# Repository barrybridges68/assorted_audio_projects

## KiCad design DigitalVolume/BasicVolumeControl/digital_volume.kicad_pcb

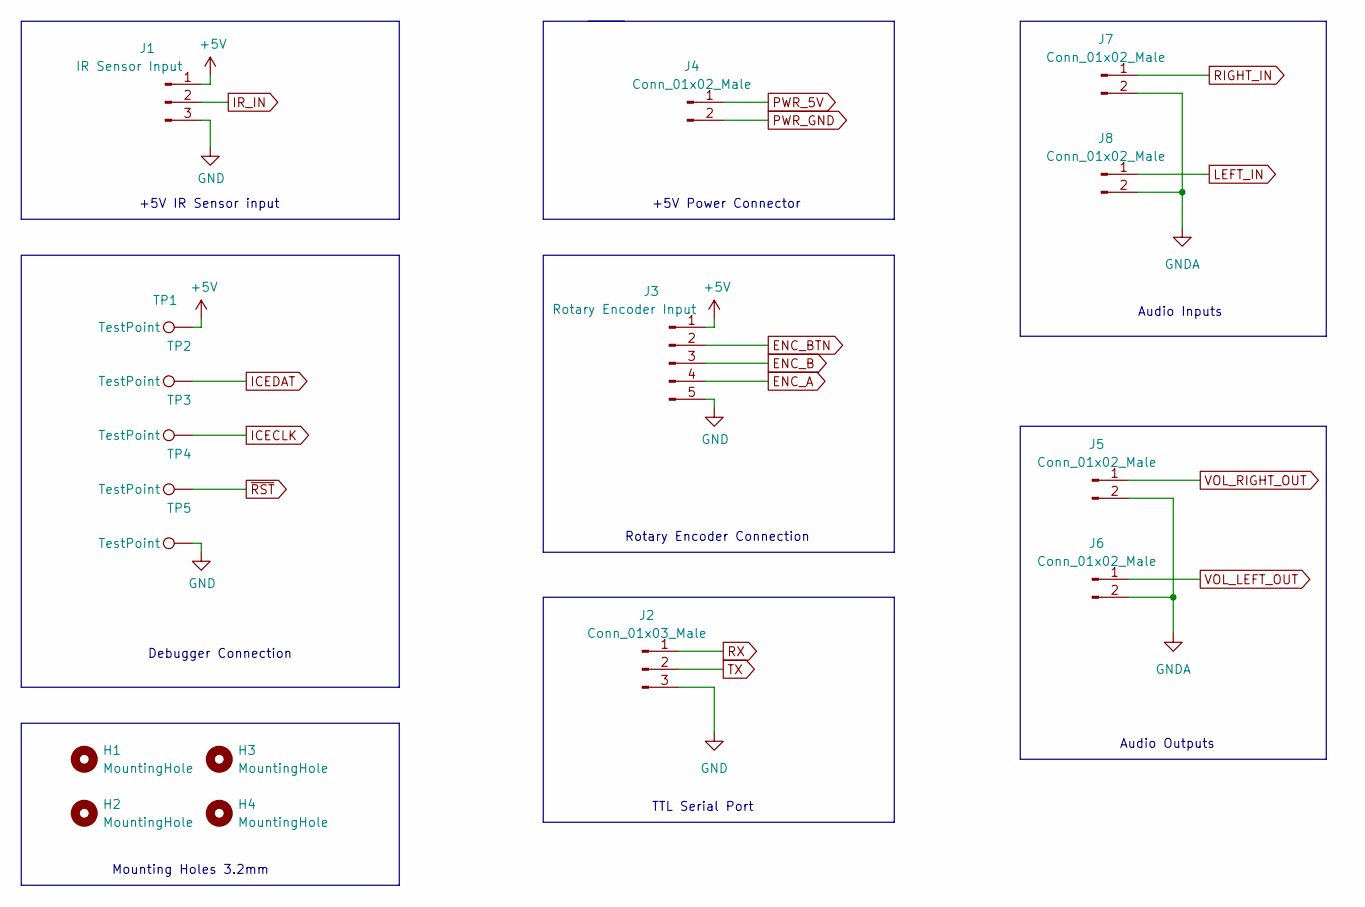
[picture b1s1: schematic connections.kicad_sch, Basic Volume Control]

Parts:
H1, H2, H3, H4: MountingHole; MountingHole_3.2mm_M3
J1: IR Sensor Input; JST_EH_B3B-EH-A_1x03_P2.50mm_Vertical
J2: Conn_01x03_Male; JST_EH_B3B-EH-A_1x03_P2.50mm_Vertical
J3: Rotary Encoder Input; JST_EH_B5B-EH-A_1x05_P2.50mm_Vertical
J4, J5, J6, J7, J8: Conn_01x02_Male; JST_EH_B2B-EH-A_1x02_P2.50mm_Vertical
TP1, TP2, TP3, TP4, TP5: TestPoint; TestPoint_Pad_1.0x1.0mm

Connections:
+5V: J1.1, J3.1, TP1.1; also elsewhere on the board
ENC_A: J3.4; also elsewhere on the board
ENC_B: J3.3; also elsewhere on the board
ENC_BTN: J3.2; also elsewhere on the board
ICECLK: TP3.1; also elsewhere on the board
ICEDAT: TP2.1; also elsewhere on the board
IR_IN: J1.2; also elsewhere on the board
LEFT_IN: J8.1; also elsewhere on the board
PWR_5V: J4.1; also elsewhere on the board
PWR_GND: J1.3, J2.3, J3.5, J4.2, J5.2, J6.2, J7.2, J8.2, TP5.1; also elsewhere on the board
RIGHT_IN: J7.1; also elsewhere on the board
RX: J2.1; also elsewhere on the board
TX: J2.2; also elsewhere on the board
VOL_LEFT_OUT: J6.1; also elsewhere on the board
VOL_RIGHT_OUT: J5.1; also elsewhere on the board
~RST: TP4.1; also elsewhere on the board

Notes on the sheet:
+5V IR Sensor input
Audio Outputs
Mounting Holes 3.2mm
Audio Inputs
Debugger Connection
+5V Power Connector
TTL Serial Port
Rotary Encoder Connection

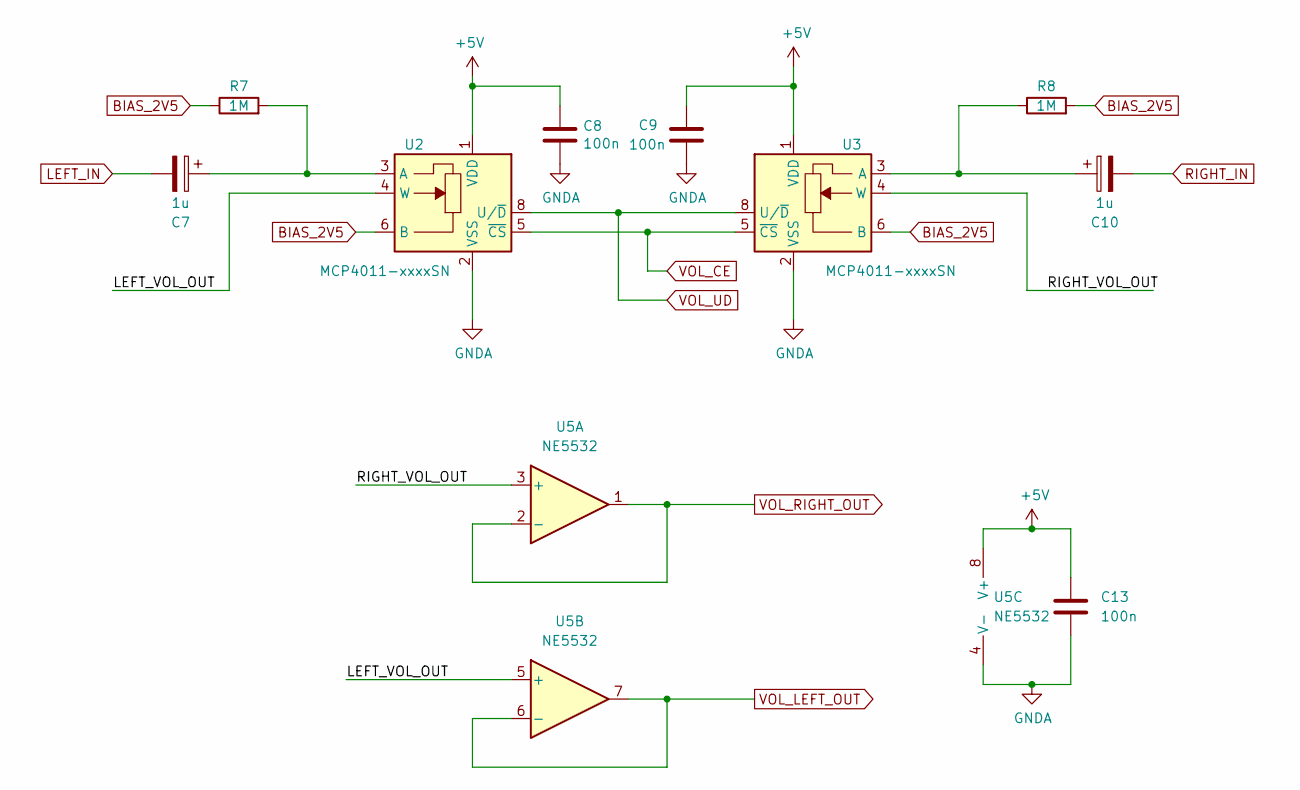
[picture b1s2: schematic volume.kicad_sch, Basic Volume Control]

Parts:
C7, C10: 1u; CP_Elec_4x5.4
C8, C9, C13: 100n; C_0603_1608Metric
R7, R8: 1M; R_0603_1608Metric
U2, U3: MCP4011-xxxxSN; SOIC-8_3.9x4.9mm_P1.27mm
U5: NE5532; SOIC-8_3.9x4.9mm_P1.27mm

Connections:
+5V: C8.1, C9.1, C13.1, U2.1 (VDD), U3.1 (VDD), U5.8 (V+); also elsewhere on the board
/volume/LEFT_VOL_OUT: U2.4 (W), U5.5 (+)
/volume/RIGHT_VOL_OUT: U3.4 (W), U5.3 (+)
BIAS_2V5: R7.1, R8.2, U2.6 (B), U3.6 (B); also elsewhere on the board
LEFT_IN: C7.2; also elsewhere on the board
unnamed: C7.1, R7.2, U2.3 (A)
unnamed: C10.1, R8.1, U3.3 (A)
PWR_GND: C8.2, C9.2, C13.2, U2.2 (VSS), U3.2 (VSS), U5.4 (V-); also elsewhere on the board
RIGHT_IN: C10.2; also elsewhere on the board
VOL_CE: U2.5 (~CS), U3.5 (~CS); also elsewhere on the board
VOL_LEFT_OUT: U5.6 (-), U5.7; also elsewhere on the board
VOL_RIGHT_OUT: U5.1, U5.2 (-); also elsewhere on the board
VOL_UD: U2.8 (U/~D), U3.8 (U/~D); also elsewhere on the board

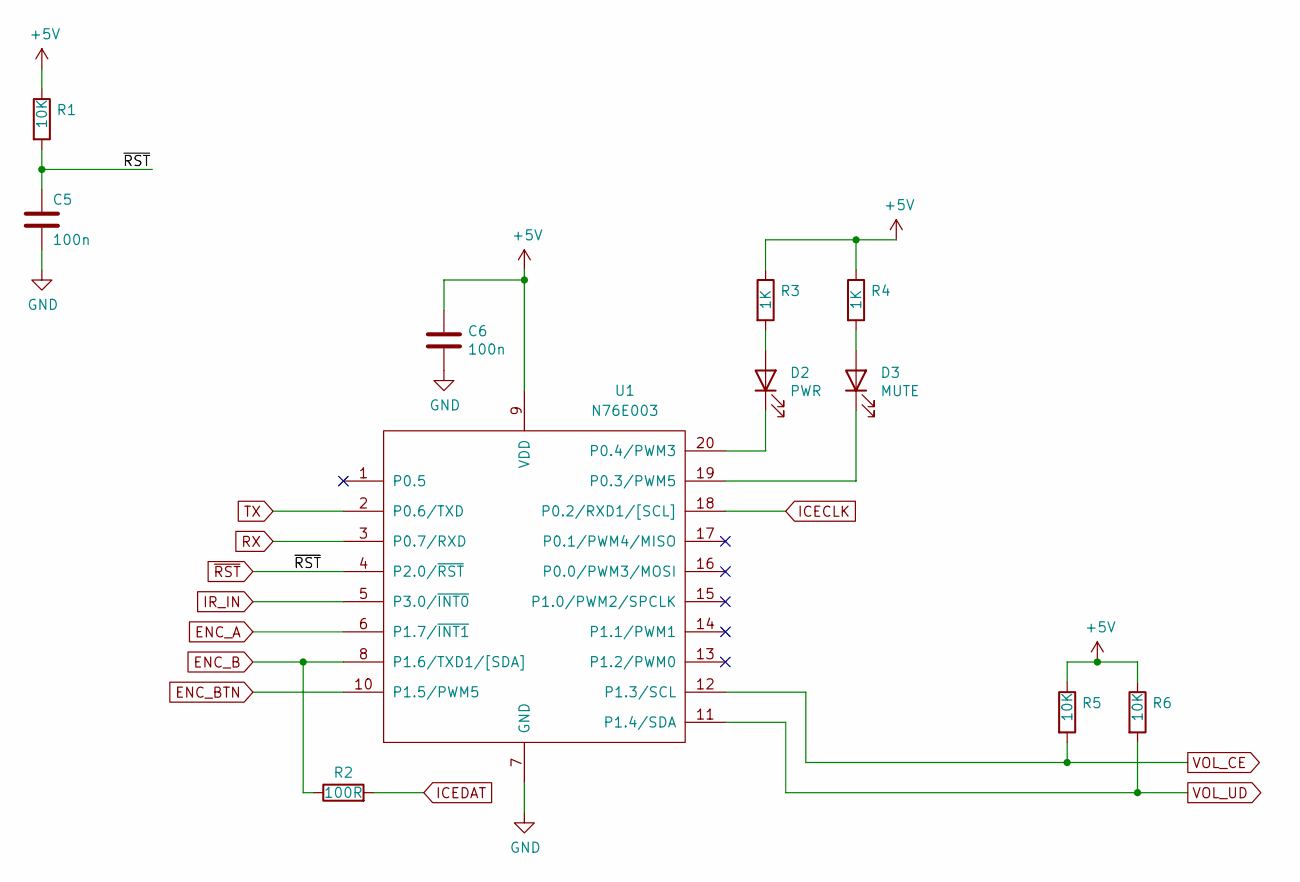
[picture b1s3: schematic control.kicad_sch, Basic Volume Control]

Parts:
C5, C6: 100n; C_0603_1608Metric
D2: PWR; LED_0603_1608Metric_Pad1.05x0.95mm_HandSolder
D3: MUTE; LED_0603_1608Metric_Pad1.05x0.95mm_HandSolder
R1, R5, R6: 10K; R_0603_1608Metric
R2: 100R; R_0603_1608Metric
R3, R4: 1K; R_0603_1608Metric
U1: N76E003; TSSOP-20_4.4x6.5mm_P0.65mm

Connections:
+5V: C6.1, R1.1, R3.1, R4.1, R5.1, R6.1, U1.9 (VDD); also elsewhere on the board
ENC_A: U1.6 (P1.7/~INT1); also elsewhere on the board
ENC_B: R2.1, U1.8 (P1.6/TXD1/[SDA]); also elsewhere on the board
ENC_BTN: U1.10 (P1.5/PWM5); also elsewhere on the board
ICECLK: U1.18 (P0.2/RXD1/[SCL]); also elsewhere on the board
ICEDAT: R2.2; also elsewhere on the board
IR_IN: U1.5 (P3.0/~INT0); also elsewhere on the board
unnamed: D2.1 (K), U1.20 (P0.4/PWM3)
unnamed: D2.2 (A), R3.2
unnamed: D3.1 (K), U1.19 (P0.3/PWM5)
unnamed: D3.2 (A), R4.2
PWR_GND: C5.2, C6.2, U1.7 (GND); also elsewhere on the board
RX: U1.3 (P0.7/RXD); also elsewhere on the board
TX: U1.2 (P0.6/TXD); also elsewhere on the board
VOL_CE: R5.2, U1.12 (P1.3/SCL); also elsewhere on the board
VOL_UD: R6.2, U1.11 (P1.4/SDA); also elsewhere on the board
~RST: C5.1, R1.2, U1.4 (P2.0/~RST); also elsewhere on the board

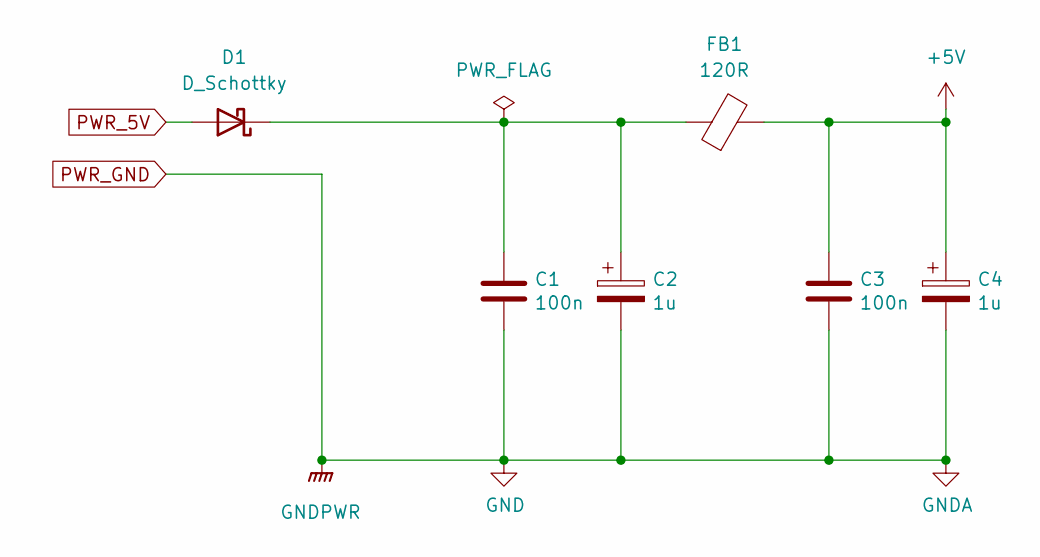
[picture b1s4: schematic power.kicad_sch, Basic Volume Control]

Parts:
C1, C3: 100n; C_0603_1608Metric
C2, C4: 1u; CP_Elec_4x5.4
D1: D_Schottky; D_0603_1608Metric_Pad1.05x0.95mm_HandSolder
FB1: 120R; R_0603_1608Metric

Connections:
+5V: C3.1, C4.1, FB1.2; also elsewhere on the board
unnamed: C1.1, C2.1, D1.1 (K), FB1.1
PWR_5V: D1.2 (A); also elsewhere on the board
PWR_GND: C1.2, C2.2, C3.2, C4.2; also elsewhere on the board

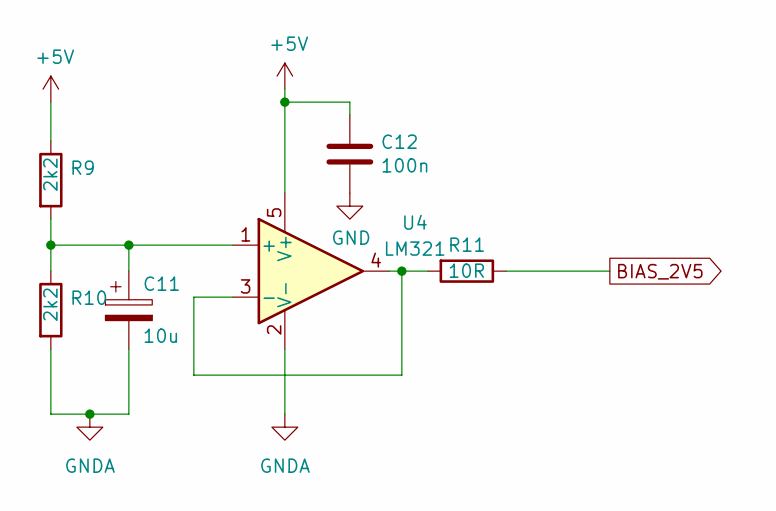
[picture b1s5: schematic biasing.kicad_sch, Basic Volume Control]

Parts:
C11: 10u; CP_Elec_4x5.4
C12: 100n; C_0603_1608Metric
R9, R10: 2k2; R_0603_1608Metric
R11: 10R; R_0603_1608Metric
U4: LM321; SOT-23-5

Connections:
+5V: C12.1, R9.1, U4.5 (V+); also elsewhere on the board
BIAS_2V5: R11.1; also elsewhere on the board
unnamed: C11.1, R9.2, R10.1, U4.1 (+)
unnamed: R11.2, U4.3 (-), U4.4
PWR_GND: C11.2, C12.2, R10.2, U4.2 (V-); also elsewhere on the board

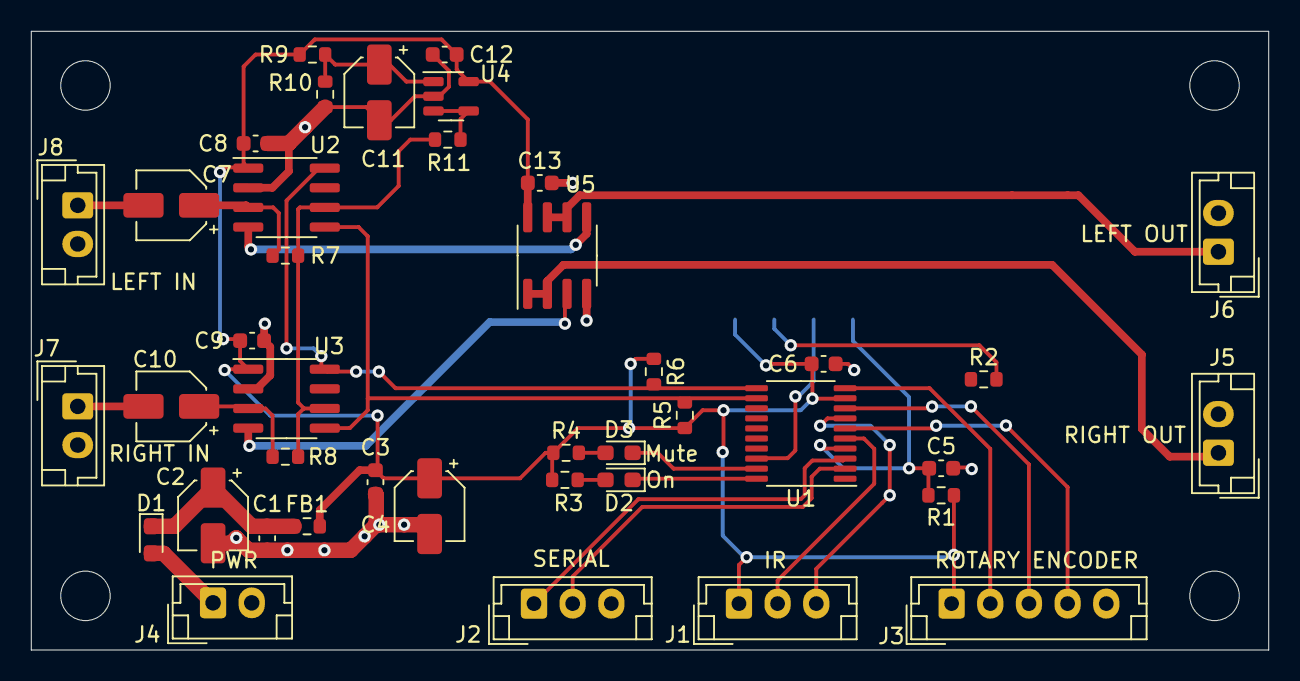
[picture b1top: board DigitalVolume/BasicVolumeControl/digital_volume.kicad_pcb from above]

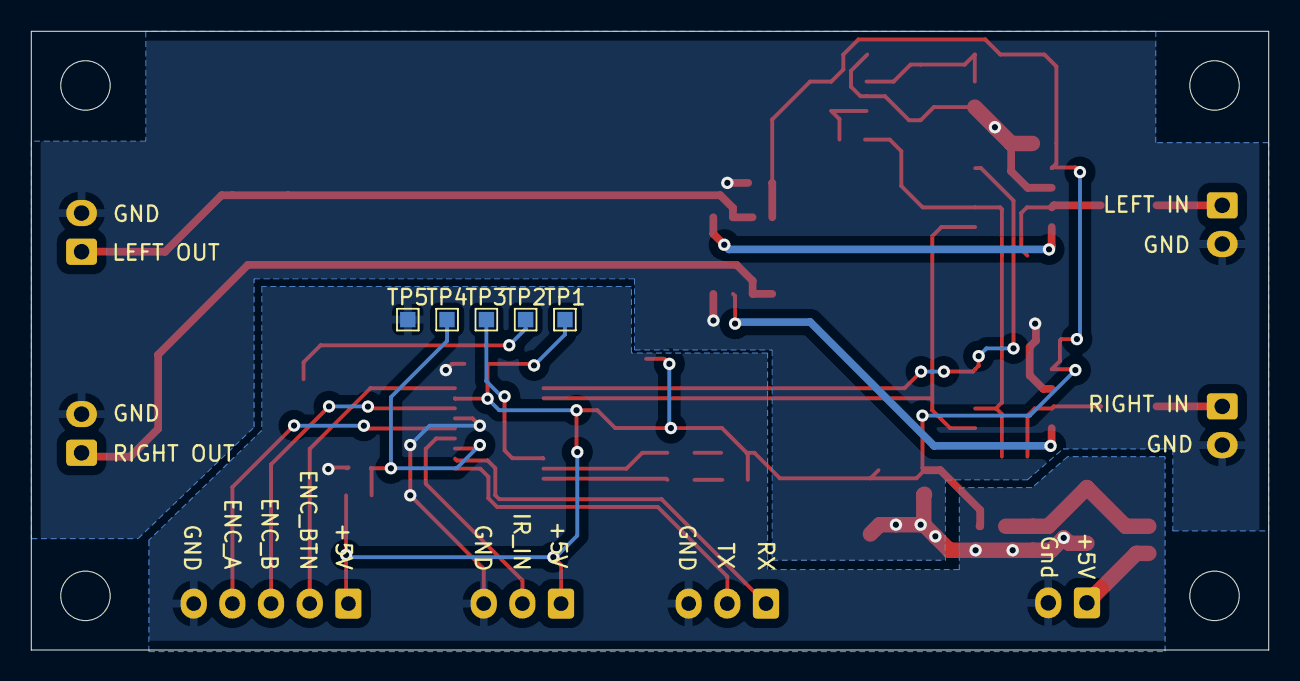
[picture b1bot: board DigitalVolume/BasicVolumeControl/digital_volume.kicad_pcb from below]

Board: 2 copper layers, 80.0 x 40.0 mm, 50 parts (5 on the bottom side), 30 nets.

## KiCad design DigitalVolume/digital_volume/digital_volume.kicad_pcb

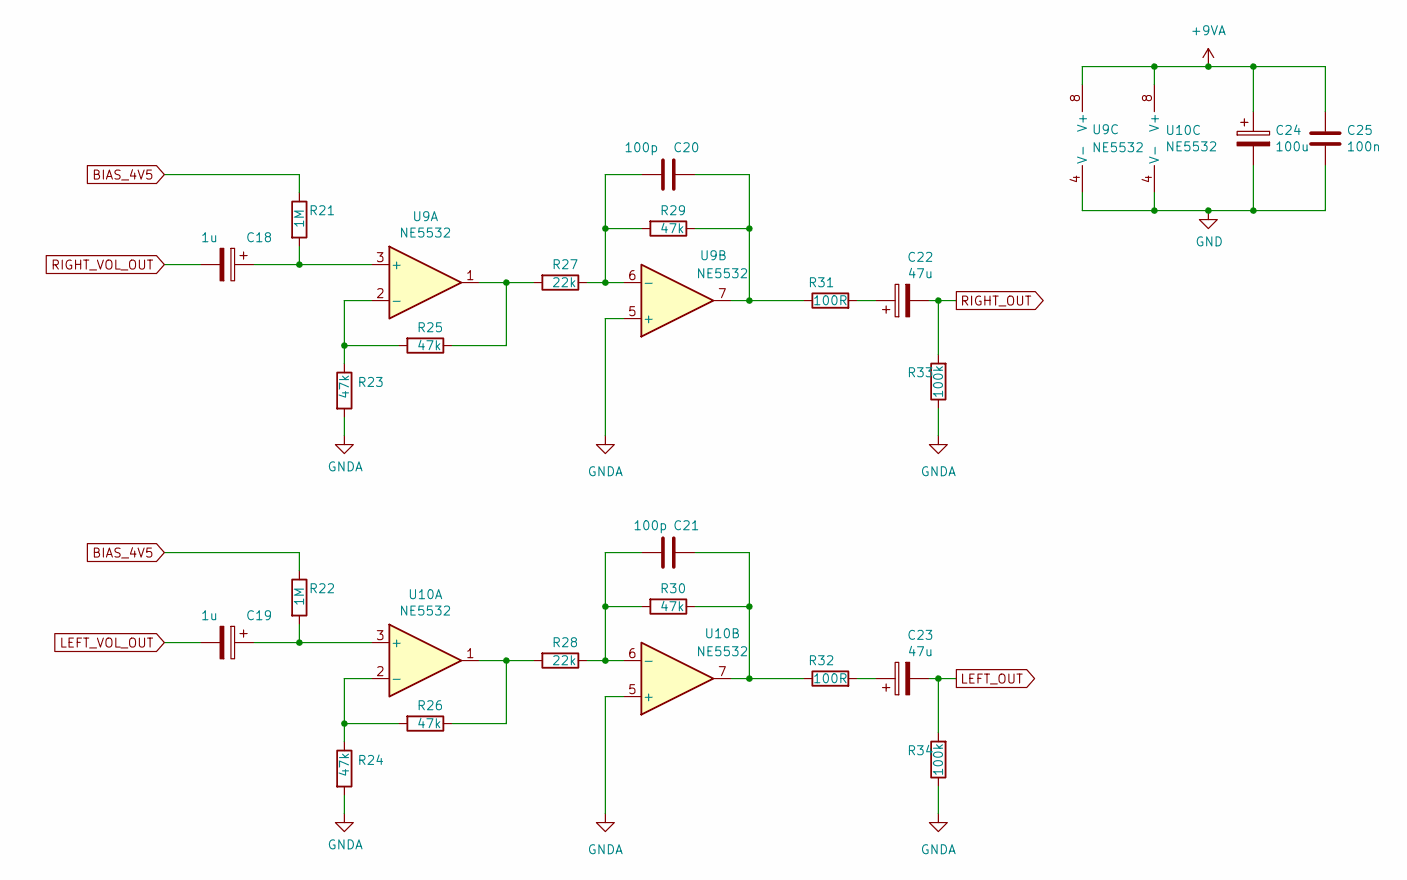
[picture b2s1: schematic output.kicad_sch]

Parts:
C18, C19: 1u; CP_Elec_4x5.4
C20, C21: 100p; C_0603_1608Metric_Pad1.08x0.95mm_HandSolder
C22, C23: 47u; CP_Elec_6.3x5.3
C24: 100u; CP_Elec_6.3x7.7
C25: 100n; C_0603_1608Metric_Pad1.08x0.95mm_HandSolder
R21, R22: 1M; R_0603_1608Metric_Pad0.98x0.95mm_HandSolder
R23, R24, R25, R26, R29, R30: 47k; R_0603_1608Metric_Pad0.98x0.95mm_HandSolder
R27, R28: 22k; R_0603_1608Metric_Pad0.98x0.95mm_HandSolder
R31, R32: 100R; R_0603_1608Metric_Pad0.98x0.95mm_HandSolder
R33, R34: 100k; R_0603_1608Metric_Pad0.98x0.95mm_HandSolder
U9, U10: NE5532; SOIC-8_3.9x4.9mm_P1.27mm

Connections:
+9VA: C24.1, C25.1, U9.8 (V+), U10.8 (V+); also elsewhere on the board
BIAS_4V5: R21.1, R22.1; also elsewhere on the board
GND: C24.2, C25.2, R23.2, R24.2, R33.1, R34.1, U9.4 (V-), U9.5 (+), U10.4 (V-), U10.5 (+); also elsewhere on the board
LEFT_OUT: C23.2, R34.2; also elsewhere on the board
LEFT_VOL_OUT: C19.2; also elsewhere on the board
unnamed: C18.1, R21.2, U9.3 (+)
unnamed: C19.1, R22.2, U10.3 (+)
unnamed: C20.1, R27.1, R29.2, U9.6 (-)
unnamed: C20.2, R29.1, R31.1, U9.7
unnamed: C21.1, R28.1, R30.2, U10.6 (-)
unnamed: C21.2, R30.1, R32.1, U10.7
unnamed: C22.1, R31.2
unnamed: C23.1, R32.2
unnamed: R23.1, R25.2, U9.2 (-)
unnamed: R24.1, R26.2, U10.2 (-)
unnamed: R25.1, R27.2, U9.1
unnamed: R26.1, R28.2, U10.1
RIGHT_OUT: C22.2, R33.2; also elsewhere on the board
RIGHT_VOL_OUT: C18.2; also elsewhere on the board

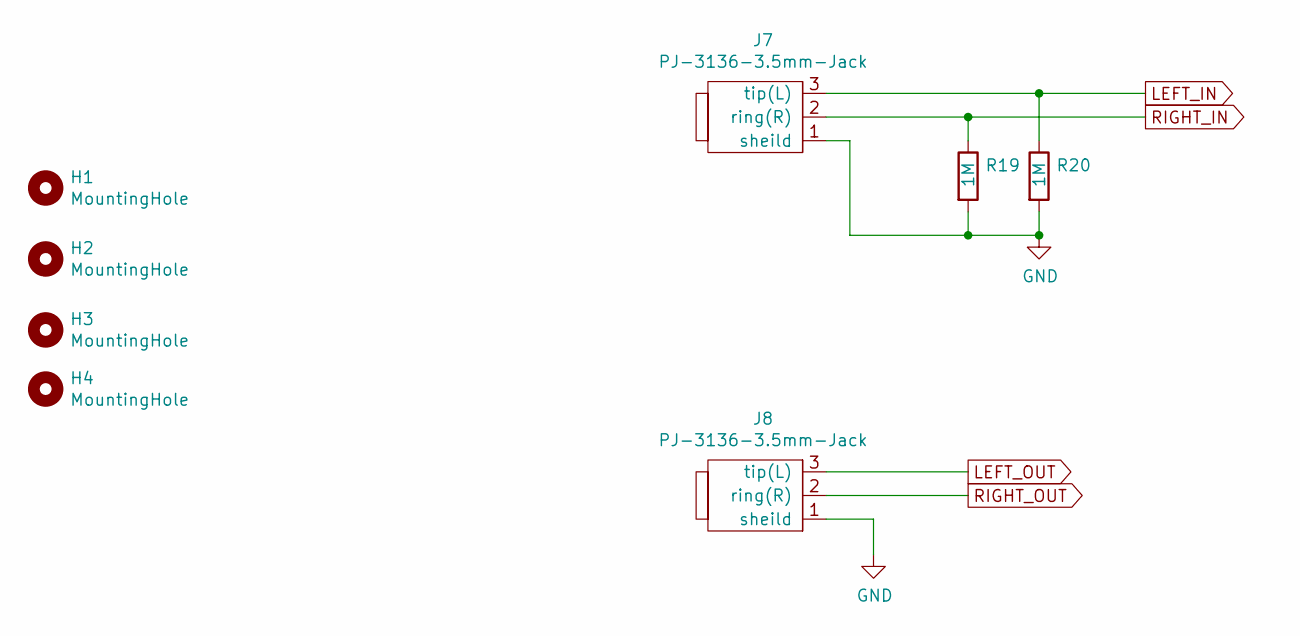
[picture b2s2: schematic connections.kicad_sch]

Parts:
H1, H2, H3, H4: MountingHole; MountingHole_3.2mm_M3
J7, J8: PJ-3136-3.5mm-Jack
R19, R20: 1M; R_0603_1608Metric_Pad0.98x0.95mm_HandSolder

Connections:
GND: J7.1 (sheild), J8.1 (sheild), R19.2, R20.2; also elsewhere on the board
LEFT_IN: J7.3 (tip(L)), R20.1; also elsewhere on the board
LEFT_OUT: J8.3 (tip(L)); also elsewhere on the board
RIGHT_IN: J7.2 (ring(R)), R19.1; also elsewhere on the board
RIGHT_OUT: J8.2 (ring(R)); also elsewhere on the board

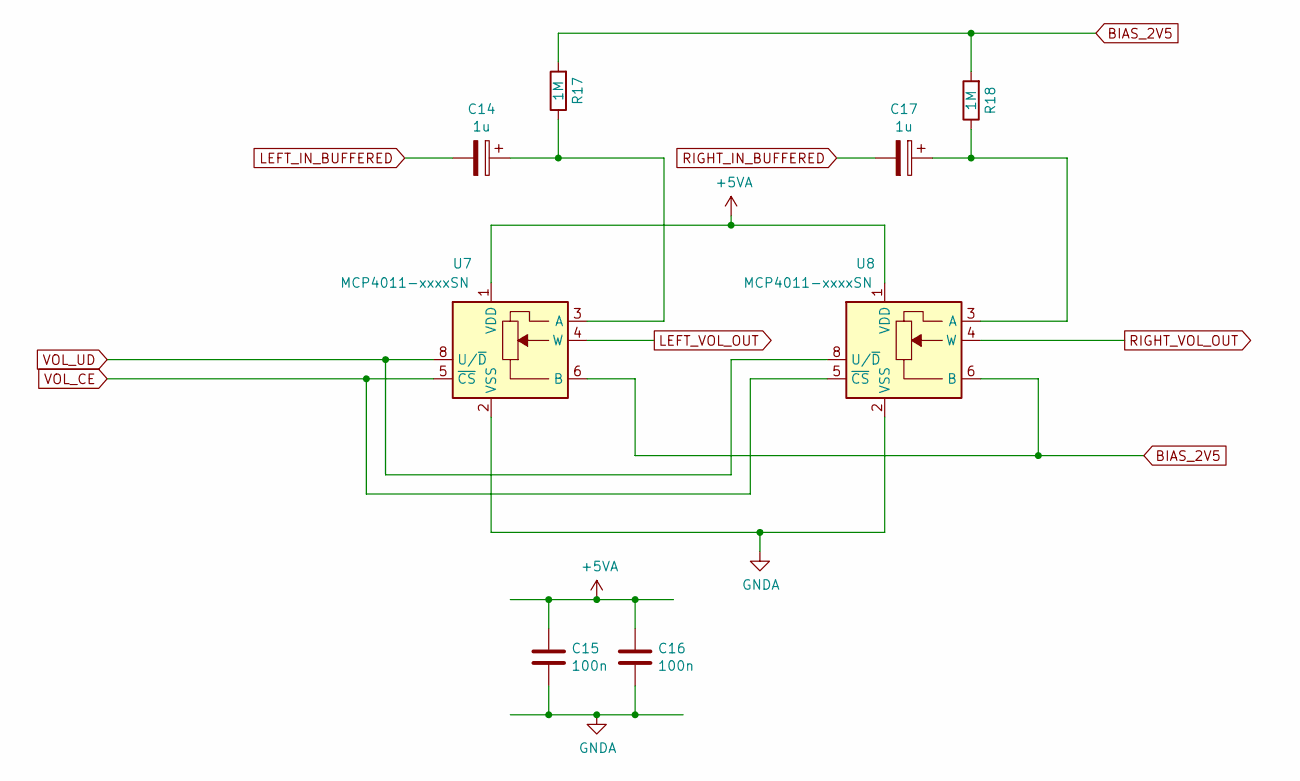
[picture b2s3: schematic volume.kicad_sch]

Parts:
C14, C17: 1u; CP_Elec_4x5.4
C15, C16: 100n; C_0603_1608Metric_Pad1.08x0.95mm_HandSolder
R17, R18: 1M; R_0603_1608Metric_Pad0.98x0.95mm_HandSolder
U7, U8: MCP4011-xxxxSN; SOIC-8_3.9x4.9mm_P1.27mm

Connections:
BIAS_2V5: R17.2, R18.2, U7.6 (B), U8.6 (B); also elsewhere on the board
GND: C15.2, C16.2, U7.2 (VSS), U8.2 (VSS); also elsewhere on the board
LEFT_IN_BUFFERED: C14.2; also elsewhere on the board
LEFT_VOL_OUT: U7.4 (W); also elsewhere on the board
unnamed: C14.1, R17.1, U7.3 (A)
unnamed: C17.1, R18.1, U8.3 (A)
RIGHT_IN_BUFFERED: C17.2; also elsewhere on the board
RIGHT_VOL_OUT: U8.4 (W); also elsewhere on the board
VOL_CE: U7.5 (~CS), U8.5 (~CS); also elsewhere on the board
VOL_UD: U7.8 (U/~D), U8.8 (U/~D); also elsewhere on the board

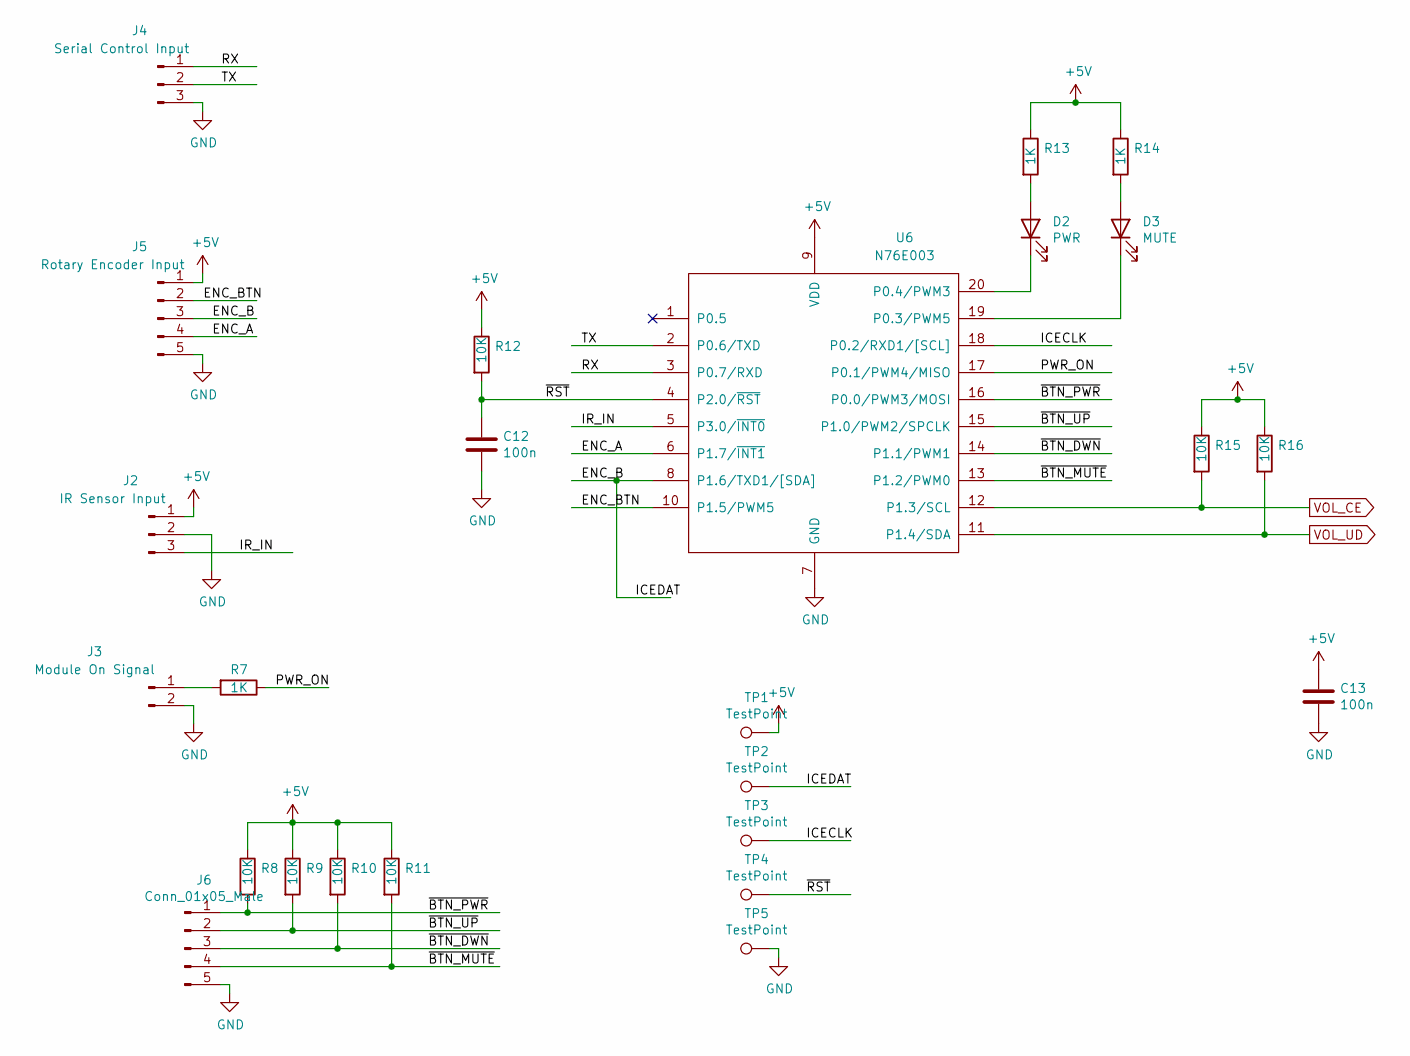
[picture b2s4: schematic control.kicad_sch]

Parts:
C12, C13: 100n; C_0603_1608Metric_Pad1.08x0.95mm_HandSolder
D2: PWR; LED_0603_1608Metric_Pad1.05x0.95mm_HandSolder
D3: MUTE; LED_0603_1608Metric_Pad1.05x0.95mm_HandSolder
J2: IR Sensor Input; JST_EH_B3B-EH-A_1x03_P2.50mm_Vertical
J3: Module On Signal; JST_EH_B2B-EH-A_1x02_P2.50mm_Vertical
J4: Serial Control Input; JST_EH_B3B-EH-A_1x03_P2.50mm_Vertical
J5: Rotary Encoder Input; JST_EH_B5B-EH-A_1x05_P2.50mm_Vertical
J6: Conn_01x05_Male; JST_EH_B5B-EH-A_1x05_P2.50mm_Vertical
R7, R13, R14: 1K; R_0603_1608Metric_Pad0.98x0.95mm_HandSolder
R8, R9, R10, R11, R12, R15, R16: 10K; R_0603_1608Metric_Pad0.98x0.95mm_HandSolder
TP1, TP2, TP3, TP4, TP5: TestPoint; TestPoint_Pad_1.0x1.0mm
U6: N76E003; TSSOP-20_4.4x6.5mm_P0.65mm

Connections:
+5V: C13.1, J2.1, J5.1, R8.1, R9.1, R10.1, R11.1, R12.1, R13.1, R14.1, R15.1, R16.1, TP1.1, U6.9 (VDD); also elsewhere on the board
/control/ENC_A: J5.4, U6.6 (P1.7/~INT1)
/control/ENC_B: J5.3, TP2.1, U6.8 (P1.6/TXD1/[SDA])
/control/ENC_BTN: J5.2, U6.10 (P1.5/PWM5)
/control/ICECLK: TP3.1, U6.18 (P0.2/RXD1/[SCL])
/control/IR_IN: J2.3, U6.5 (P3.0/~INT0)
/control/PWR_ON: R7.1, U6.17 (P0.1/PWM4/MISO)
/control/RX: J4.1, U6.3 (P0.7/RXD)
/control/TX: J4.2, U6.2 (P0.6/TXD)
/control/~BTN_DWN: J6.3, R10.2, U6.14 (P1.1/PWM1)
/control/~BTN_MUTE: J6.4, R11.2, U6.13 (P1.2/PWM0)
/control/~BTN_PWR: J6.1, R8.2, U6.16 (P0.0/PWM3/MOSI)
/control/~BTN_UP: J6.2, R9.2, U6.15 (P1.0/PWM2/SPCLK)
/control/~RST: C12.1, R12.2, TP4.1, U6.4 (P2.0/~RST)
GND: C12.2, C13.2, J2.2, J3.2, J4.3, J5.5, J6.5, TP5.1, U6.7 (GND); also elsewhere on the board
unnamed: D2.1 (K), U6.20 (P0.4/PWM3)
unnamed: D2.2 (A), R13.2
unnamed: D3.1 (K), U6.19 (P0.3/PWM5)
unnamed: D3.2 (A), R14.2
unnamed: J3.1, R7.2
VOL_CE: R15.2, U6.12 (P1.3/SCL); also elsewhere on the board
VOL_UD: R16.2, U6.11 (P1.4/SDA); also elsewhere on the board

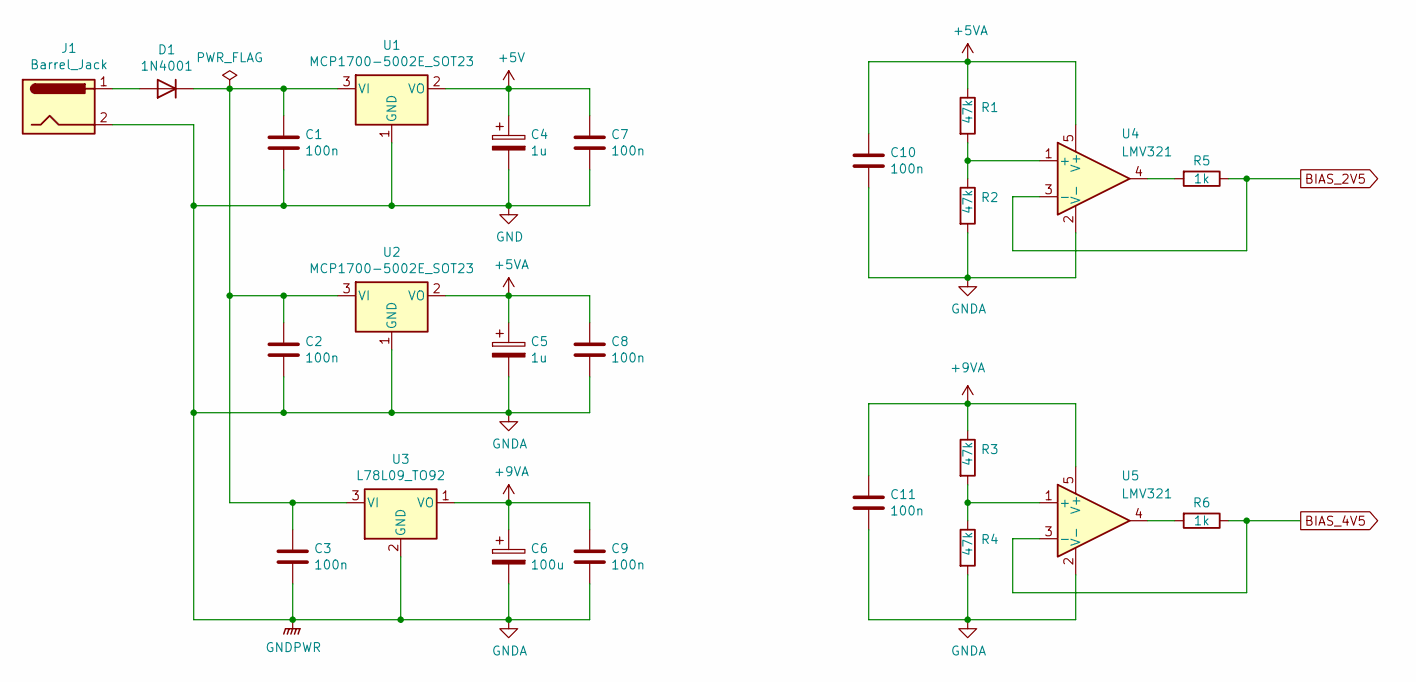
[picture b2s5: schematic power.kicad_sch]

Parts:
C1, C2, C3: 100n; C_0603_1608Metric_Pad1.05x0.95mm_HandSolder
C4, C5: 1u; CP_Elec_6.3x7.7
C6: 100u; CP_Elec_6.3x7.7
C7, C8, C9, C10, C11: 100n; C_0603_1608Metric_Pad1.08x0.95mm_HandSolder
D1: 1N4001; D_SOD-123F
J1: Barrel_Jack; BarrelJack_Horizontal
R1, R2, R3, R4: 47k; R_0603_1608Metric_Pad0.98x0.95mm_HandSolder
R5, R6: 1k; R_0603_1608Metric_Pad0.98x0.95mm_HandSolder
U1, U2: MCP1700-5002E_SOT23; SOT-23
U3: L78L09_TO92; TO-92_Inline
U4, U5: LMV321; SOT-23-5_HandSoldering

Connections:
+5V: C4.1, C7.1, U1.2 (VO); also elsewhere on the board
+9VA: C6.1, C9.1, C11.1, R3.1, U3.1 (VO), U5.5 (V+); also elsewhere on the board
BIAS_2V5: R5.1, U4.3 (-); also elsewhere on the board
BIAS_4V5: R6.1, U5.3 (-); also elsewhere on the board
GND: C1.2, C2.2, C3.2, C4.2, C5.2, C6.2, C7.2, C8.2, C9.2, C10.2, C11.2, J1.2, R2.2, R4.2, U1.1 (GND), U2.1 (GND), U3.2 (GND), U4.2 (V-), U5.2 (V-); also elsewhere on the board
unnamed: D1.2 (A), J1.1
unnamed: R1.2, R2.1, U4.1 (+)
unnamed: R3.2, R4.1, U5.1 (+)
unnamed: R5.2, U4.4
unnamed: R6.2, U5.4

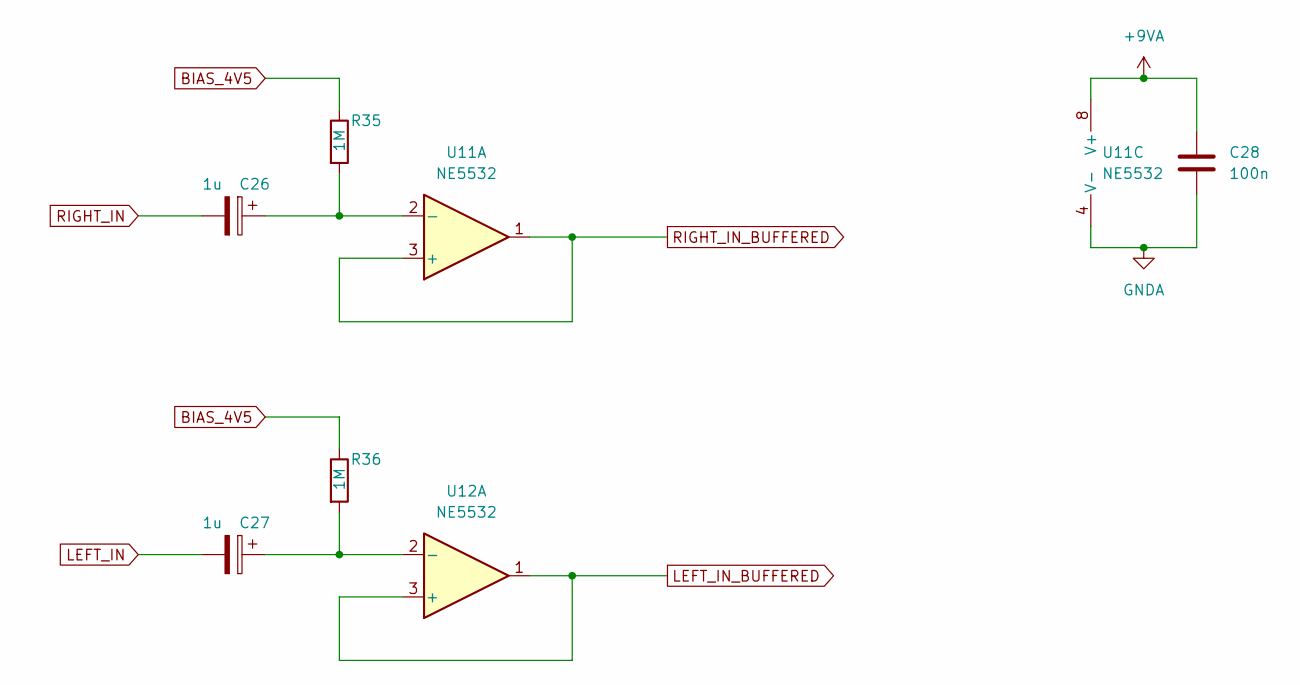
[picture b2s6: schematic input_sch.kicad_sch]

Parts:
C26, C27: 1u; CP_Elec_6.3x5.3
C28: 100n; C_0603_1608Metric_Pad1.08x0.95mm_HandSolder
R35, R36: 1M; R_0603_1608Metric_Pad0.98x0.95mm_HandSolder
U11, U12: NE5532; SOIC-8_3.9x4.9mm_P1.27mm

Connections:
+9VA: C28.1, U11.8 (V+); also elsewhere on the board
BIAS_4V5: R35.1, R36.1; also elsewhere on the board
GND: C28.2, U11.4 (V-); also elsewhere on the board
LEFT_IN: C27.2; also elsewhere on the board
LEFT_IN_BUFFERED: U12.1, U12.3 (+); also elsewhere on the board
unnamed: C26.1, R35.2, U11.2 (-)
unnamed: C27.1, R36.2, U12.2 (-)
RIGHT_IN: C26.2; also elsewhere on the board
RIGHT_IN_BUFFERED: U11.1, U11.3 (+); also elsewhere on the board

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
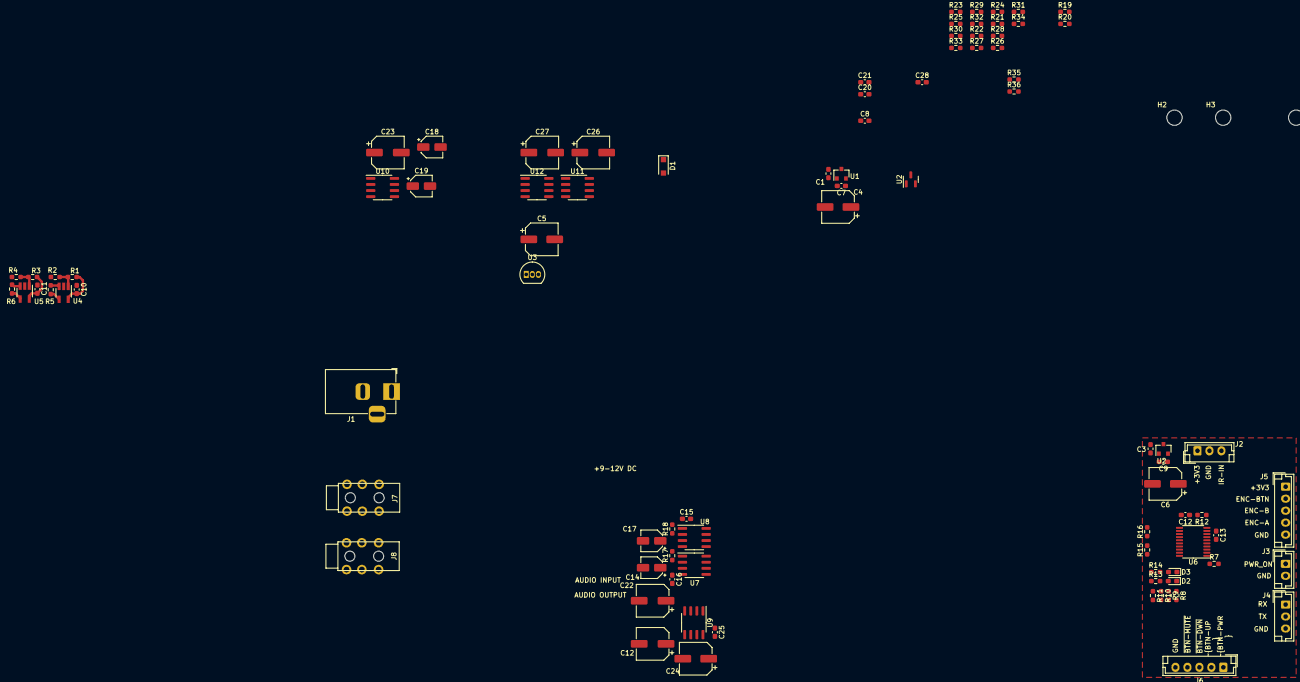
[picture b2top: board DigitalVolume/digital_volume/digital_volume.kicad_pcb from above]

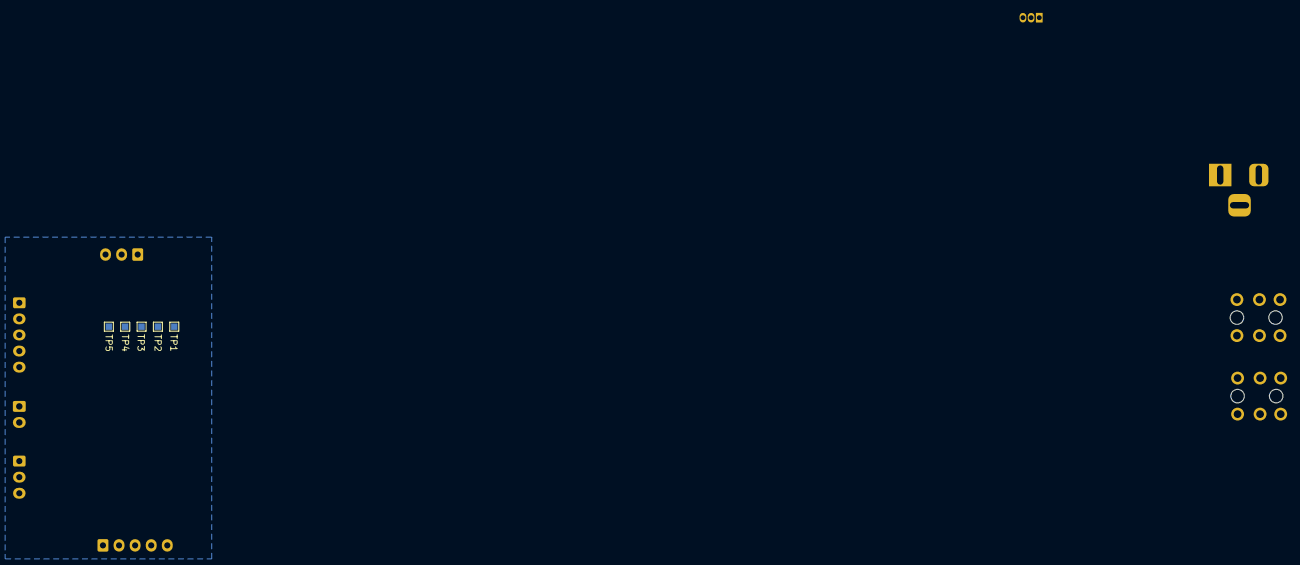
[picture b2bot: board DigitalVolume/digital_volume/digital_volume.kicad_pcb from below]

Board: 2 copper layers, 97 parts (5 on the bottom side), 56 nets.

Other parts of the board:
C12#2: 47u; CP_Elec_6.3x5.3
U2#2: MCP1700-5002E_SOT23; SOT-23

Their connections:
GND: U2#2.1 (GND); also elsewhere on the board
LEFT_OUT: C12#2.2; also elsewhere on the board

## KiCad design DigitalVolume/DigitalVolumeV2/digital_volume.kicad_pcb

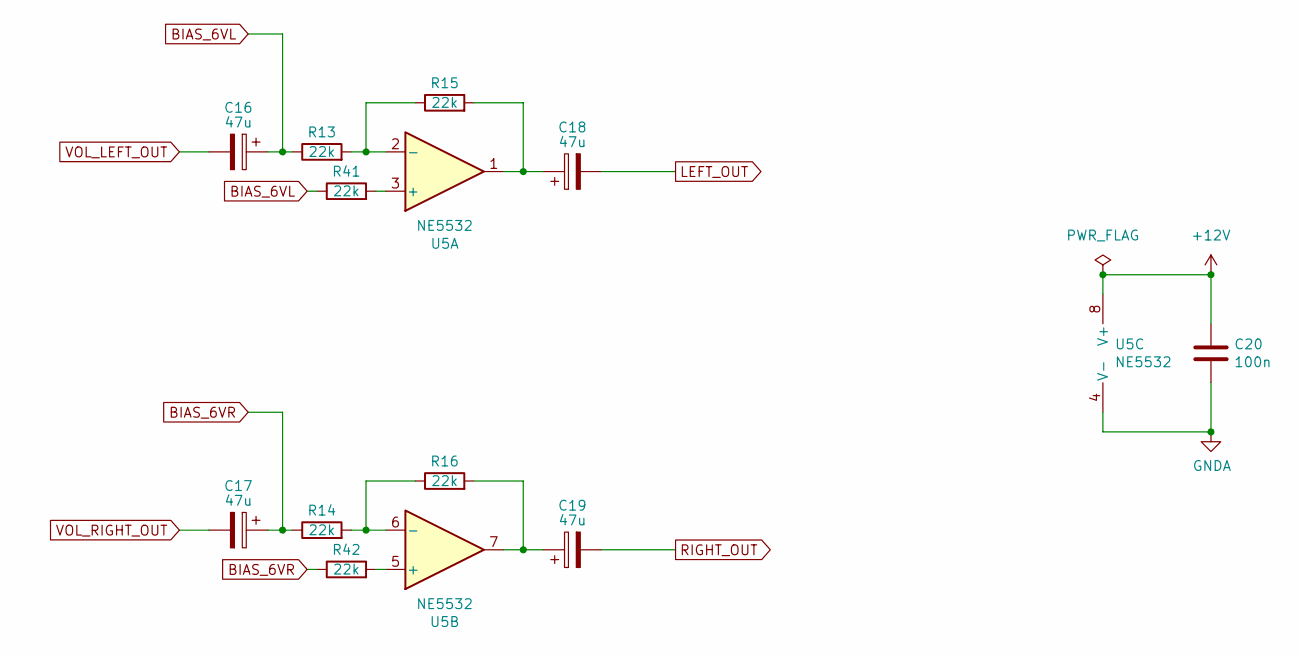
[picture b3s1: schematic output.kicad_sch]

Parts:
C16, C17, C18, C19: 47u; CP_Elec_6.3x5.3
C20: 100n; C_0603_1608Metric
R13, R14, R15, R16, R41, R42: 22k; R_0603_1608Metric
U5: NE5532; SOIC-8_3.9x4.9mm_P1.27mm

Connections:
+12V: C20.1, U5.8 (V+); also elsewhere on the board
BIAS_6VL: C16.1, R13.1, R41.1; also elsewhere on the board
BIAS_6VR: C17.1, R14.1, R42.1; also elsewhere on the board
GND: C20.2, U5.4 (V-); also elsewhere on the board
LEFT_OUT: C18.2; also elsewhere on the board
unnamed: C18.1, R15.2, U5.1
unnamed: C19.1, R16.2, U5.7
unnamed: R13.2, R15.1, U5.2 (-)
unnamed: R14.2, R16.1, U5.6 (-)
unnamed: R41.2, U5.3 (+)
unnamed: R42.2, U5.5 (+)
RIGHT_OUT: C19.2; also elsewhere on the board
VOL_LEFT_OUT: C16.2; also elsewhere on the board
VOL_RIGHT_OUT: C17.2; also elsewhere on the board
